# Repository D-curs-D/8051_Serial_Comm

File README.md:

# 8051_Serial_Comm
8051 based serial communication. The PCB Design was done on KiCAD, the simulations were done using proteus and code on keil studios. It was a test project 😆

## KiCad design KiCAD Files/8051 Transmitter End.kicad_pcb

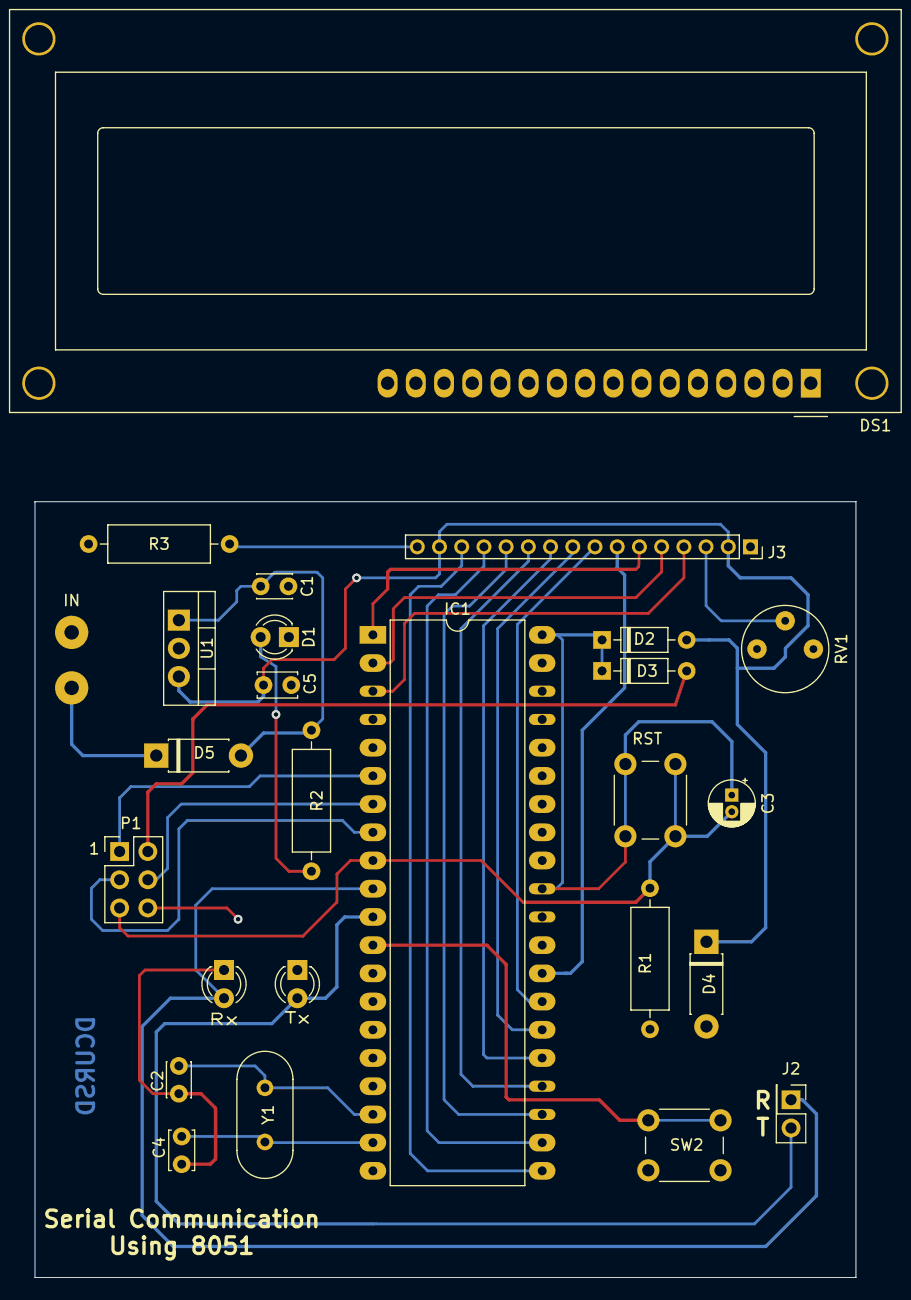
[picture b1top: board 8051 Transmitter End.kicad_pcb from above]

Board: 2 copper layers, 73.9 x 69.8 mm, 26 parts (0 on the bottom side), 29 nets.

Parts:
C1: 100nF; C_Disc_D3.0mm_W2.0mm_P2.50mm
C2: 22pF; C_Disc_D3.0mm_W2.0mm_P2.50mm
C3: 10uF; CP_Radial_D4.0mm_P1.50mm
C4: 22pF; C_Disc_D3.4mm_W2.1mm_P2.50mm
C5: 10nF; C_Disc_D3.4mm_W2.1mm_P2.50mm
D1: Blue; LED_D3.0mm
D2, D3: 1N5818; D_DO-35_SOD27_P7.62mm_Horizontal
D4, D5: 1N4007; D_DO-41_SOD81_P7.62mm_Horizontal
DS1: WC1602A
IC1: AT89S52-24PU; DIP-40_W15.24mm_LongPads
J1: Screw_Terminal_01x02; AKL_5_2
J2: Conn_02x01; PinHeader_2x01_P2.54mm_Vertical
J3: Conn_01x16_Female; PinSocket_1x16_P2.00mm_Vertical
P1: CONN_02X03; PinHeader_2x03_P2.54mm_Vertical
R1: 10k; R_Axial_DIN0309_L9.0mm_D3.2mm_P12.70mm_Horizontal
R2: 330; R_Axial_DIN0309_L9.0mm_D3.2mm_P12.70mm_Horizontal
R3: 220; R_Axial_DIN0309_L9.0mm_D3.2mm_P12.70mm_Horizontal
RST: SW_SPST; SW_PUSH_6mm_H4.3mm
RV1: 10k; Potentiometer_Bourns_3339P_Vertical_HandSoldering
Rx: LED_Small; LED_D3.0mm
SW2: SW_SPST; SW_PUSH_6mm_H4.3mm
Tx: LED_Small; LED_D3.0mm
U1: LM7805_TO220; TO-220-3_Vertical
Y1: Crystal_Small; Crystal_HC49-4H_Vertical

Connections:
DATA0: DS1.7, IC1.28, J3.7
DATA1: DS1.8, IC1.27, J3.8
DATA2: DS1.9, IC1.26, J3.9
DATA3: DS1.10, IC1.25, J3.10
DATA4: DS1.11, IC1.24, J3.11
DATA5: DS1.12, IC1.23, J3.12
DATA6: DS1.13, IC1.22, J3.13
DATA7: DS1.14, IC1.21, J3.14
EN: DS1.6, IC1.1, J3.6
GND: C1.2, C2.2, C4.2, C5.2, D1.1, D4.2, DS1.1, IC1.20, J1.2, J3.1, P1.6, R1.2, R3.2, RV1.3, Rx.1, SW2.1, Tx.1, U1.2
MISO: IC1.7, P1.4
MOSI: IC1.6, P1.1
unnamed: D1.2, R2.2
unnamed: D5.1, J1.1
unnamed: DS1.3, J3.3, RV1.2
unnamed: DS1.16, J3.16, R3.1
unnamed: IC1.12, SW2.2
RESET: C3.2, IC1.9, P1.5, R1.1, RST.1
RS: DS1.4, IC1.3, J3.4
RW: DS1.5, IC1.2, J3.5
Rx: IC1.10, J2.1, Rx.2
SCK: IC1.8, P1.3
Tx: IC1.11, J2.2, Tx.2
VCC: C1.1, D5.2, R2.1, U1.1
Vin: C3.1, D2.1, D3.1, IC1.31, IC1.40, RST.2
Vin1: C5.1, D2.2, D4.1, DS1.2, DS1.15, J3.2, J3.15, U1.3
Vin2: D3.2, P1.2
XTAL1: C4.1, IC1.19, Y1.2
XTAL2: C2.1, IC1.18, Y1.1

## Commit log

2021-11-29 Kicad pcb files addition
2021-11-29 Minor fixes to the netlist
